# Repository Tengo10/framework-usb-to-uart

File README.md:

# framework-usb-to-uart
USB to UART Expansion Card for the Framework Laptop

## Info
*Currently an early version, design untested*

A USB to UART converter based on the CP2102 chip by Silicon Labs, also includes an external 3.3V LDO for more power than the integrated on.

### Design Goals

 - almost no extended JLC SMT parts
 - no FTDI parts
 - at least 150 mA @ 3.3V

## Todo

- Do cost optimization
- find a good LDO (AMS out of stock)
- fix some SMT data

## Manufacture
Parts, PCB and Assembly at JLC PCB are about 24€ for 5 PCBs, 2 assembled.

## Legal
Based on the reference design by the Framework Team. Not responsible for anything. Design provided as is.

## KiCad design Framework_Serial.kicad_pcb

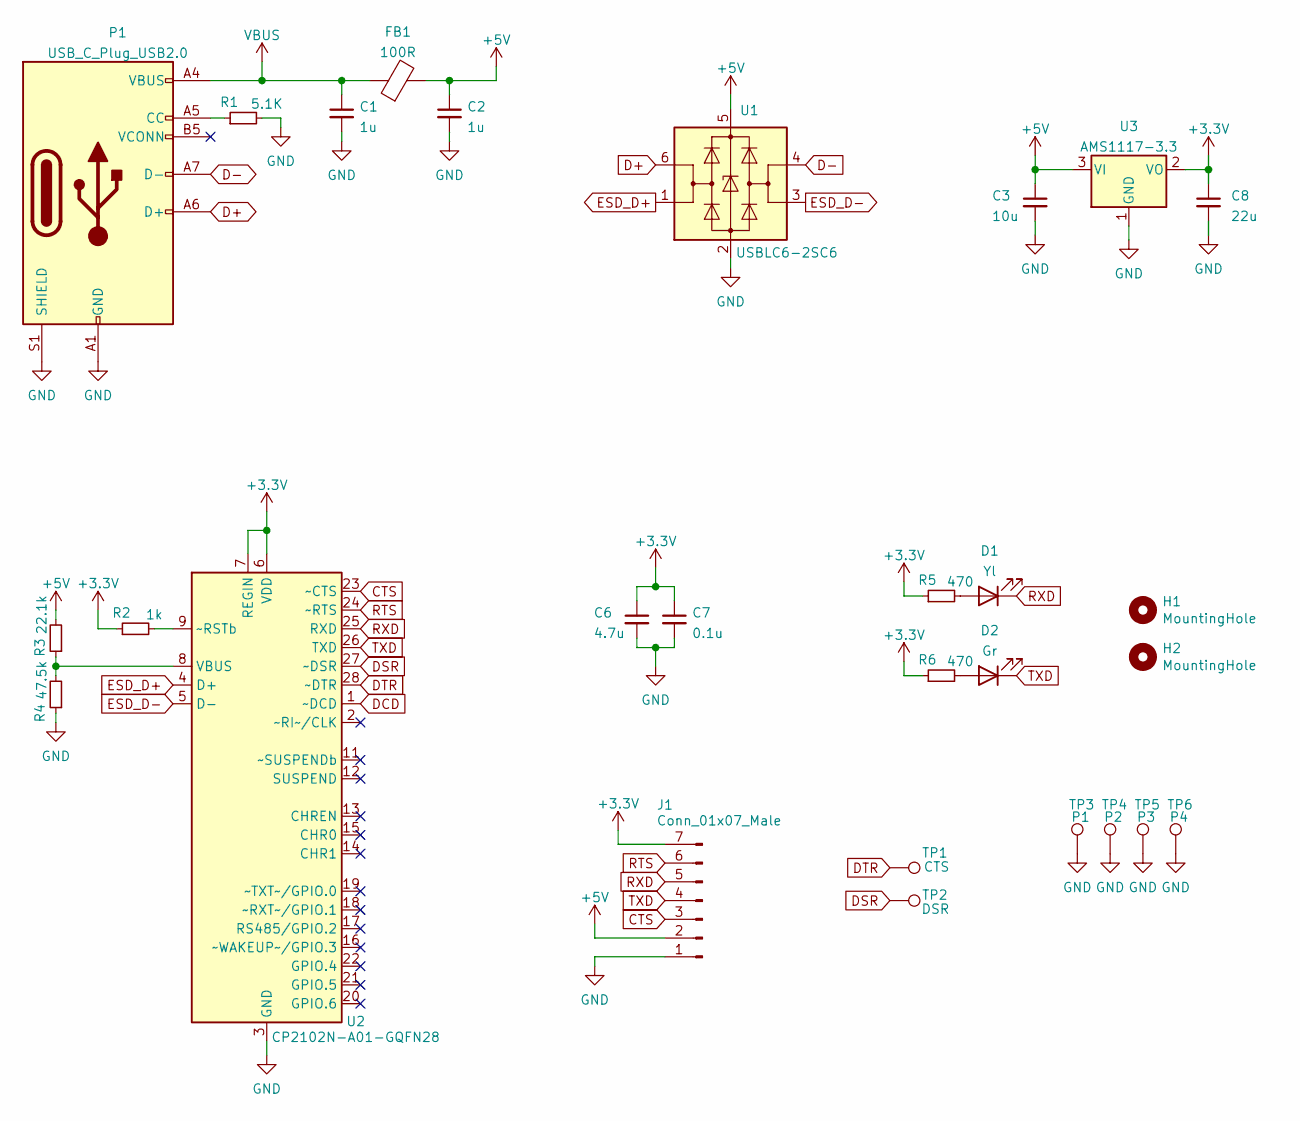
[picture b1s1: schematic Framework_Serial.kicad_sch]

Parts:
C1, C2: 1u; C_0603_1608Metric; LCSC Part # C15849
C3: 10u; C_0603_1608Metric; LCSC Part # C19702
C6: 4.7u; C_0603_1608Metric; LCSC Part # C19666
C7: 0.1u; C_0402_1005Metric; LCSC Part # C1525
C8: 22u; C_0805_2012Metric; LCSC Part # C45783
D1: Yl; LED_0603_1608Metric; LCSC Part # C72038
D2: Gr; LED_0603_1608Metric; LCSC Part # C72043
FB1: 100R; L_0805_2012Metric; LCSC Part # C1015
H1, H2: MountingHole; MountingHole_2.2mm_M2
J1: Conn_01x07_Male; PinHeader_1x07_P2.54mm_Horizontal
P1: USB_C_Plug_USB2.0; USB_C_Plug_Molex_105444
R1: 5.1K; R_0402_1005Metric; LCSC Part # C25905
R2: 1k; R_0402_1005Metric; LCSC Part # C11702
R3: 22.1k; R_0402_1005Metric; LCSC Part # C25768
R4: 47.5k; R_0402_1005Metric; LCSC Part # C25792
R5, R6: 470; R_0603_1608Metric; LCSC Part # C17710
TP1: CTS; TestPoint_Pad_D1.0mm
TP2: DSR; TestPoint_Pad_D1.0mm
TP3: P1; TestPoint_Pad_1.5x1.5mm
TP4: P2; TestPoint_Pad_1.5x1.5mm
TP5: P3; TestPoint_Pad_1.5x1.5mm
TP6: P4; TestPoint_Pad_1.5x1.5mm
U1: USBLC6-2SC6; SOT-23-6; LCSC Part # C7519
U2: CP2102N-A01-GQFN28; QFN-28-1EP_5x5mm_P0.5mm_EP3.35x3.35mm; LCSC Part # C6568
U3: AMS1117-3.3; SOT-223-3_TabPin2; LCSC Part # C6186

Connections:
+3V3: C6.1, C7.1, C8.1, J1.7, R2.1, R5.1, R6.1, U2.6 (VDD), U2.7 (REGIN), U3.2 (VO)
+5V: C2.1, C3.1, FB1.2, J1.2, R3.2, U1.5 (VBUS), U3.3 (VI)
CTS: J1.3, U2.23 (~CTS)
D+: P1.A6 (D+), U1.6 (I/O1)
D-: P1.A7 (D-), U1.4 (I/O2)
DCD: U2.1 (~DCD)
DSR: TP2.1, U2.27 (~DSR)
DTR: TP1.1, U2.28 (~DTR)
ESD_D+: U1.1 (I/O1), U2.4 (D+)
ESD_D-: U1.3 (I/O2), U2.5 (D-)
GND: C1.2, C2.2, C3.2, C6.2, C7.2, C8.2, J1.1, P1.A1 (GND), P1.A12 (GND), P1.B1 (GND), P1.B12 (GND), P1.S1 (SHIELD), R1.2, R4.1, TP3.1, TP4.1, TP5.1, TP6.1, U1.2 (GND), U2.3 (GND), U2.29 (GND), U3.1 (GND)
unnamed: D1.2 (A), R5.2
unnamed: D2.2 (A), R6.2
unnamed: P1.A5 (CC), R1.1
unnamed: R2.2, U2.9 (~RSTb)
unnamed: R3.1, R4.2, U2.8 (VBUS)
RTS: J1.6, U2.24 (~RTS)
RXD: D1.1 (K), J1.5, U2.25 (RXD)
TXD: D2.1 (K), J1.4, U2.26 (TXD)
VBUS: C1.1, FB1.1, P1.A4 (VBUS), P1.A9 (VBUS), P1.B4 (VBUS), P1.B9 (VBUS)

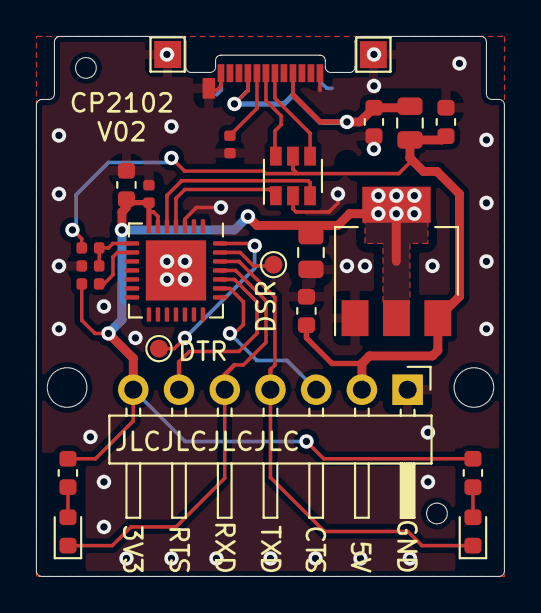
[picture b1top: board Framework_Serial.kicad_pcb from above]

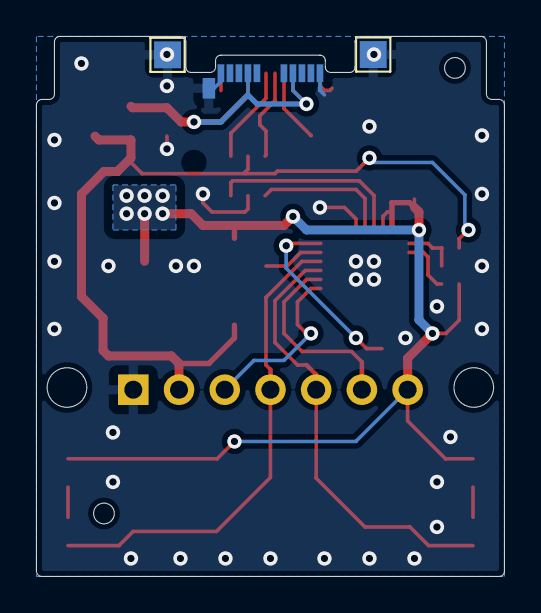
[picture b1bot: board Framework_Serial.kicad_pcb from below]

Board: 2 copper layers, 26.0 x 30.0 mm, 28 parts (2 on the bottom side), 19 nets.

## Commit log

2021-08-08 Update README.md
    added some info
2021-08-08 Add files via upload
    added initial design file version
2021-08-08 added pcb render
2021-08-09 BOM and placement files
2021-08-09 added gerber files of V02
2021-08-09 moved components around: v02
2021-08-09 added testpoints, changed to AMS1117-3.3
2021-08-09 added files
2021-08-09 updated to V2
2021-08-09 Update README.md
    updated readme
2021-08-09 Update README.md
    fixed typo
2021-08-09 removed unnecessary Vias
2021-08-09 changed LCSC parts number for LED resistor
2021-08-09 Update README.md
    added design goals and info
2021-08-09 fixed annoying highlighting
2021-08-09 added .gitignore
2021-08-09 removed backups
